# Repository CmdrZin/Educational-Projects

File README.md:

# Educational-Projects
A group of educational projects to promote hardware and software development.
Zip files of projects can be found at [https://www.gameactive.org/dist/](https://www.gameactive.org/dist/)

==================

Educational projects

|        Name          | Description                                                |
|----------------------|------------------------------------------------------------|
| IntroToArduino  | An Educational package on how to program using the Arduino IDE.|
| Beyond Arduino | A guide to learning the AVR series of microcontrollers.|

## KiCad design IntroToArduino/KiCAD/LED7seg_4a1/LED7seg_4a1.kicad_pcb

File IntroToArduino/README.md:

# Introduction to Arduino Project

An educational project with Syllabus, Instructor's guide, and Student Handout for learning coding using the Arduino IDE.

==================

|        Name         | Description                                                |
|---------------------|------------------------------------------------------------|
|DataSheets | Data sheets for devices used in the examples.|  
|ITA\_Examples | Source code for coding projects used in the sections.|   
|KiCAD | KiCAD project source for the helper boards used in the sections.|  
|A000066-full-pinout.pdf | Arduino UNO 3 pin outs.|  
|IntroToArduino.pdf | Syllabus for the course.|  
|IntoToArduino\_Instructor.pdf | Instructor's guide for the course.|  
|IntoToArduino\_Student.pdf | Student handout for the course.|

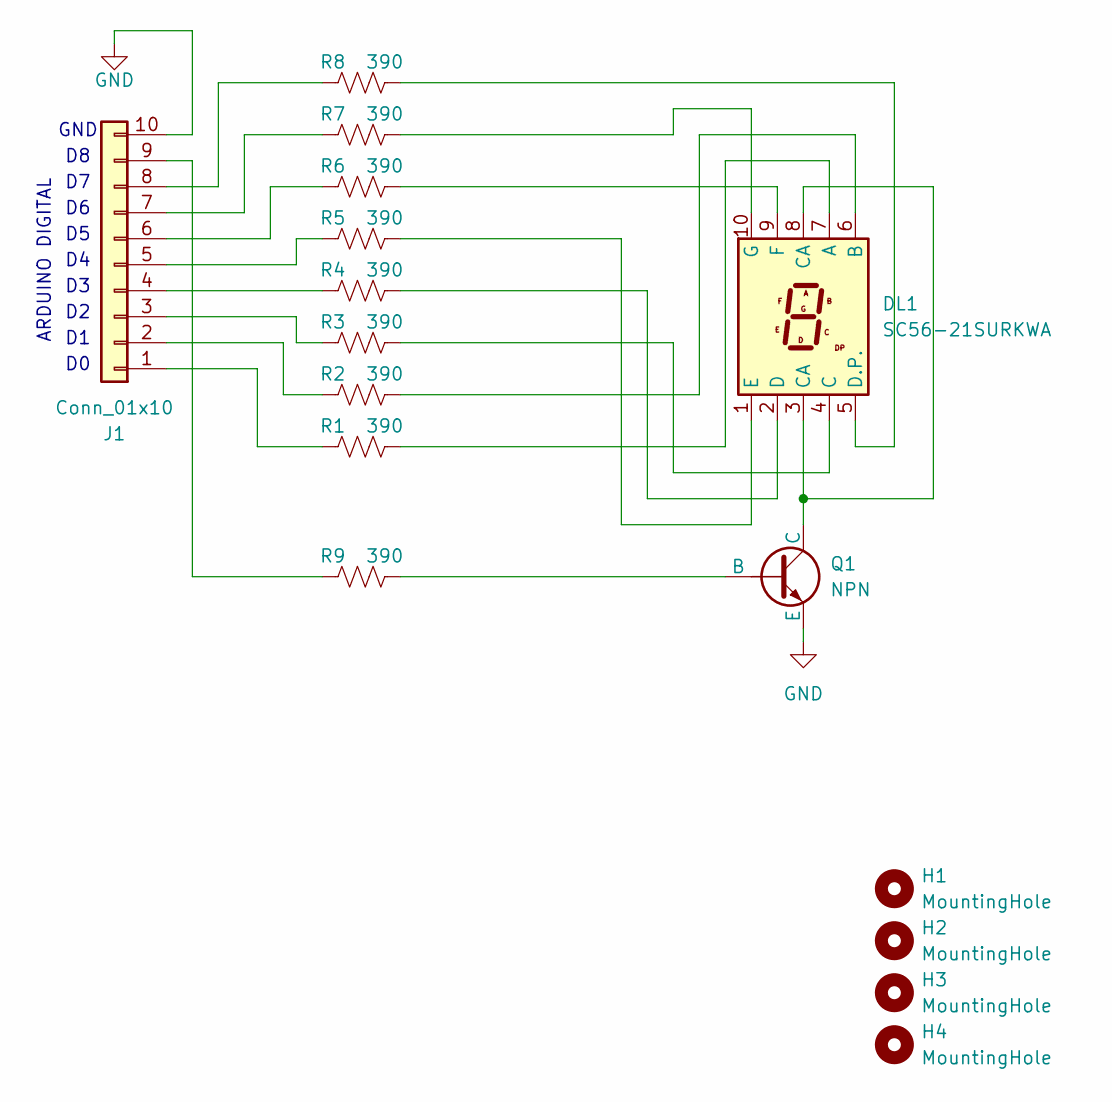
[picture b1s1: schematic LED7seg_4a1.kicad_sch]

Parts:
DL1: SC56-21SURKWA
H1, H2, H3, H4: MountingHole; MountingHole_3.2mm_M3
J1: Conn_01x10; PinSocket_1x10_P2.54mm_Vertical
Q1: NPN; TO-92
R1, R2, R3, R4, R5, R6, R7, R8, R9: 390; R_Axial_DIN0207_L6.3mm_D2.5mm_P10.16mm_Horizontal

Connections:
GND: J1.10, Q1.3 (E)
unnamed: DL1.7 (A), R1.2
unnamed: DL1.6 (B), R2.2
unnamed: DL1.4 (C), R3.2
unnamed: DL1.2 (D), R4.2
unnamed: DL1.5 (D.P.), R8.2
unnamed: DL1.1 (E), R5.2
unnamed: DL1.9 (F), R6.2
unnamed: DL1.10 (G), R7.2
unnamed: J1.1, R1.1
unnamed: J1.2, R2.1
unnamed: J1.3, R3.1
unnamed: J1.4, R4.1
unnamed: J1.5, R5.1
unnamed: J1.6, R6.1
unnamed: J1.7, R7.1
unnamed: J1.8, R8.1
unnamed: J1.9, R9.1
unnamed: Q1.2 (B), R9.2
unnamed: DL1.3 (CA), DL1.8 (CA), Q1.1 (C)

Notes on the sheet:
GND
ARDUINO DIGITAL

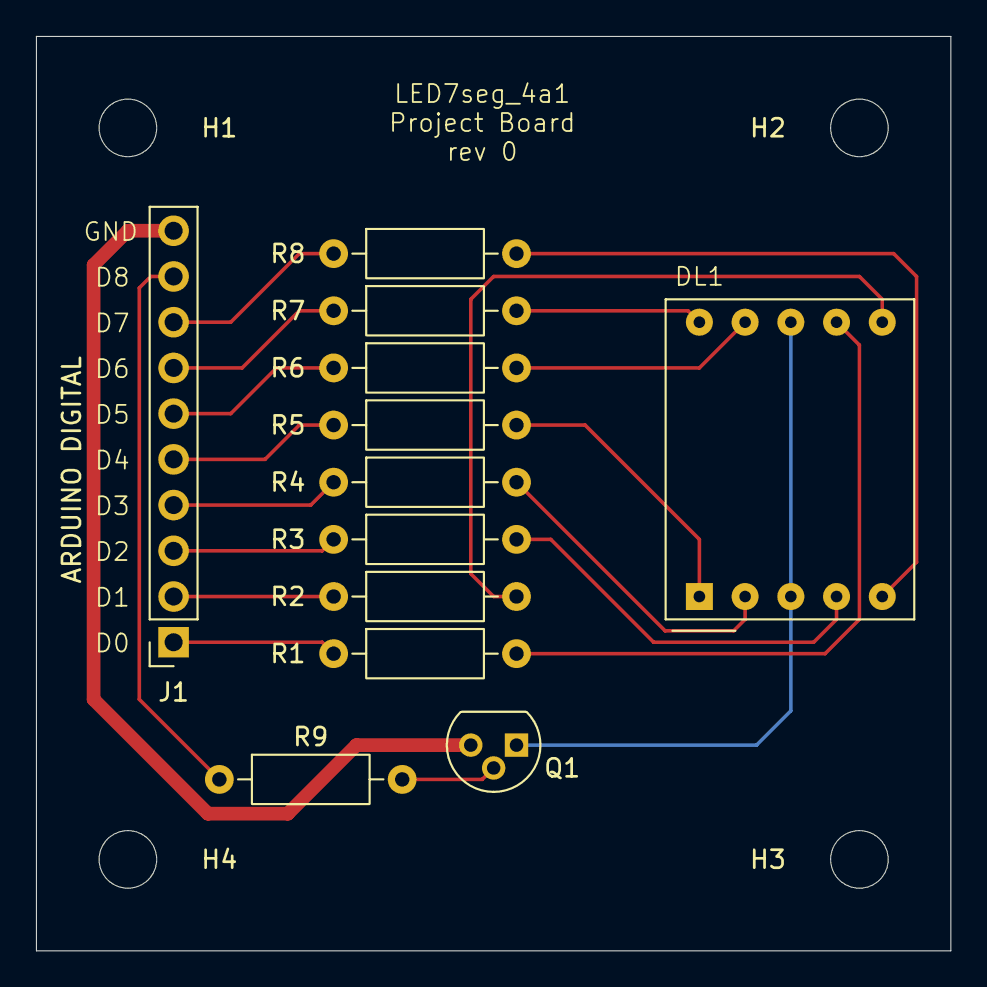
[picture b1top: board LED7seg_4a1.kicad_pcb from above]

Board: 2 copper layers, 50.8 x 50.8 mm, 16 parts (0 on the bottom side), 20 nets.

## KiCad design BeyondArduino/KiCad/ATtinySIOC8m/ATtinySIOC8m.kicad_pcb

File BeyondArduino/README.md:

# Beyond Arduino Project

A guide for learning how to use the Microchip AVR series of microcontrollers.

==================

|        Name         | Description                                                |
|---------------------|------------------------------------------------------------|
|DataSheets | Data sheets for devices used in the examples.|  
|KiCAD | KiCAD project source for the helper boards used in the sections.|  
|Projects | Source code for coding projects used in the sections.|  
|IntroToMC.pdf | Handbook guide.|  
|DDS\_Notes.pdf | Notes for developing DDS for audio generation.|

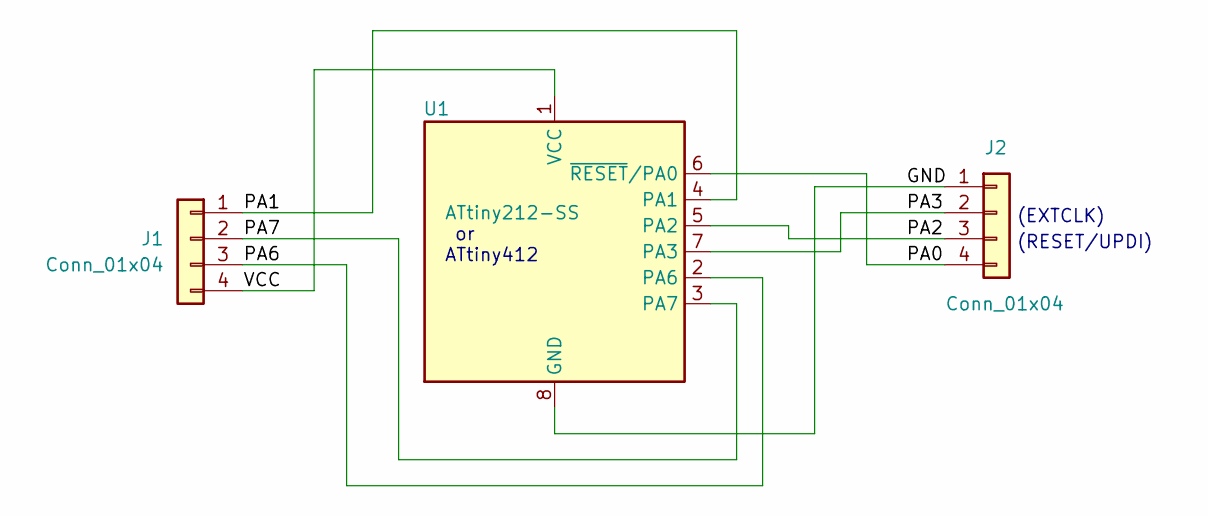
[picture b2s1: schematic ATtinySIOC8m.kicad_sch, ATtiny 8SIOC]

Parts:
J1, J2: Conn_01x04; PinHeader_1x04_P2.54mm_Vertical
U1: ATtiny212-SS; SOIC-8_3.9x4.9mm_P1.27mm

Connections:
/GND: J2.1, U1.8 (GND)
/PA0: J2.4, U1.6 (~RESET/PA0)
/PA1: J1.1, U1.4 (PA1)
/PA2: J2.3, U1.5 (PA2)
/PA3: J2.2, U1.7 (PA3)
/PA6: J1.3, U1.2 (PA6)
/PA7: J1.2, U1.3 (PA7)
/VCC: J1.4, U1.1 (VCC)

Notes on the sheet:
(RESET/UPDI)
(EXTCLK)
or ATtiny412

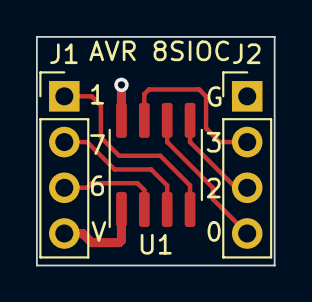
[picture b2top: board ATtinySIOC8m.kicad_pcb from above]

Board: 2 copper layers, 13.2 x 12.7 mm, 3 parts (0 on the bottom side), 8 nets.

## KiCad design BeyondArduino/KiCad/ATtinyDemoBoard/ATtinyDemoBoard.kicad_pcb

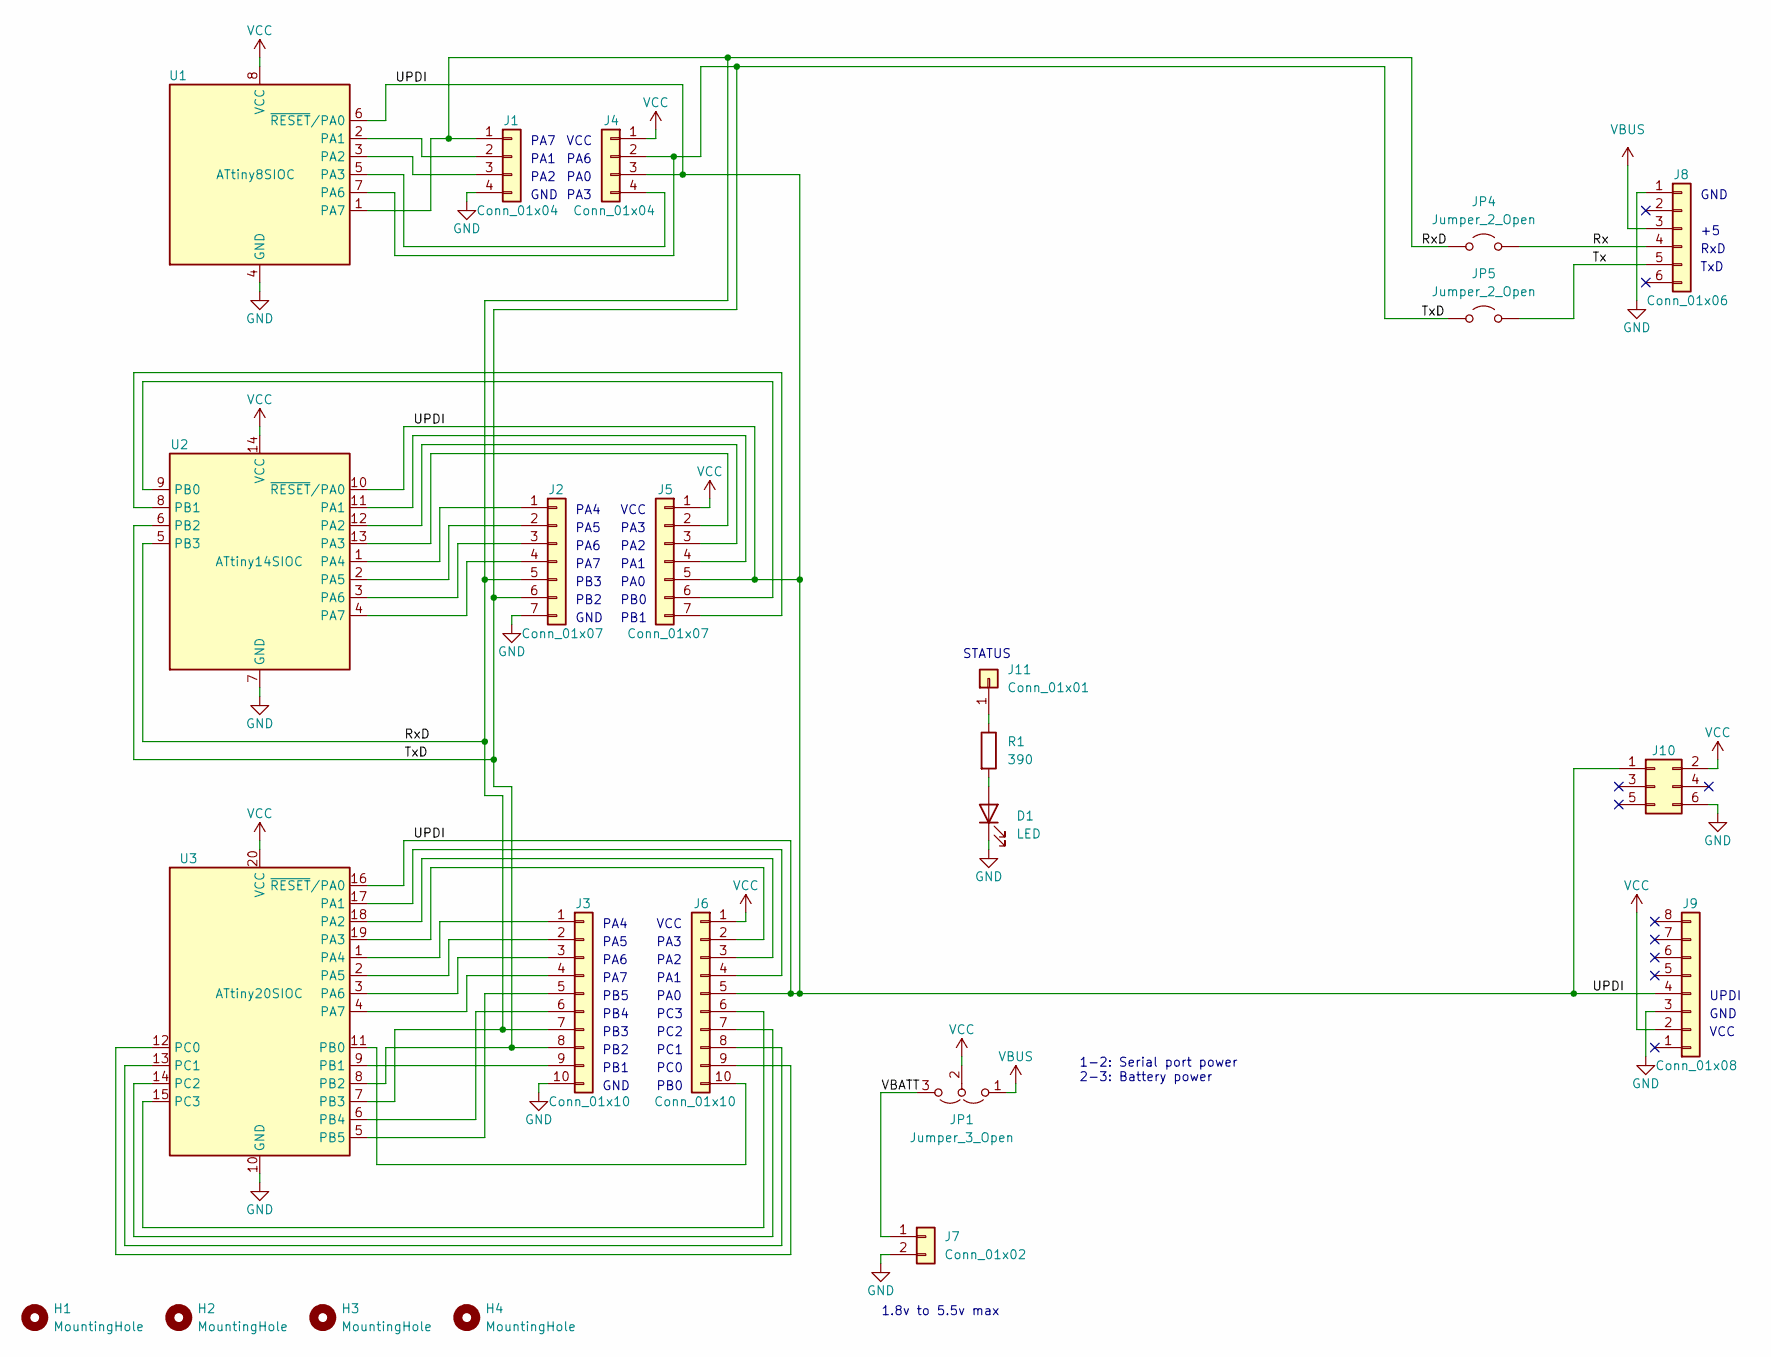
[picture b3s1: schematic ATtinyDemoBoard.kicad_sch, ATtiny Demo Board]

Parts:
D1: LED; D_0805_2012Metric_Pad1.15x1.40mm_HandSolder
H1, H2, H3, H4: MountingHole; MountingHole_3.2mm_M3
J1, J4: Conn_01x04; PinHeader_1x04_P2.54mm_Vertical
J2, J5: Conn_01x07; PinHeader_1x07_P2.54mm_Vertical
J3, J6: Conn_01x10; PinHeader_1x10_P2.54mm_Vertical
J7: Conn_01x02; PinSocket_1x02_P2.54mm_Vertical
J8: Conn_01x06; PinSocket_1x06_P2.54mm_Horizontal__FTDI
J9: Conn_01x08; PinSocket_1x08_P2.54mm_Horizontal
J10: Conn_02x03_Odd_Even; PinHeader_2x03_P2.54mm_Vertical
J11: Conn_01x01; PinSocket_1x01_P2.54mm_Vertical
JP1: Jumper_3_Open; PinSocket_1x03_P2.54mm_Vertical
JP4, JP5: Jumper_2_Open; PinSocket_1x02_P2.54mm_Vertical
R1: 390; R_0805_2012Metric_Pad1.20x1.40mm_HandSolder
U1: ATtiny8SIOC; ATtiny8SIOC-BB
U2: ATtiny14SIOC; ATtiny14SIOC-BB
U3: ATtiny20SIOC; ATtiny20SIOC-BB

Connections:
/Rx: J8.4, JP4.2 (B)
/RxD: J1.1, J2.5, J3.7, JP4.1 (A), U1.1 (PA7), U2.5 (PB3), U3.7 (PB3)
/Tx: J8.5, JP5.2 (B)
/TxD: J2.6, J3.8, J4.2, JP5.1 (A), U1.7 (PA6), U2.6 (PB2), U3.8 (PB2)
/UPDI: J4.3, J5.5, J6.5, J9.4, J10.1, U1.6 (~RESET/PA0), U2.10 (~RESET/PA0), U3.16 (~RESET/PA0)
/VBATT: J7.1, JP1.3 (B)
GND: D1.1 (K), J1.4, J2.7, J3.10, J7.2, J8.1, J9.3, J10.6, U1.4 (GND), U2.7 (GND), U3.10 (GND)
unnamed: D1.2 (A), R1.2
unnamed: J1.2, U1.2 (PA1)
unnamed: J1.3, U1.3 (PA2)
unnamed: J2.1, U2.1 (PA4)
unnamed: J2.2, U2.2 (PA5)
unnamed: J2.3, U2.3 (PA6)
unnamed: J2.4, U2.4 (PA7)
unnamed: J3.1, U3.1 (PA4)
unnamed: J3.2, U3.2 (PA5)
unnamed: J3.3, U3.3 (PA6)
unnamed: J3.4, U3.4 (PA7)
unnamed: J3.5, U3.5 (PB5)
unnamed: J3.6, U3.6 (PB4)
unnamed: J3.9, U3.9 (PB1)
unnamed: J4.4, U1.5 (PA3)
unnamed: J5.2, U2.13 (PA3)
unnamed: J5.3, U2.12 (PA2)
unnamed: J5.4, U2.11 (PA1)
unnamed: J5.6, U2.9 (PB0)
unnamed: J5.7, U2.8 (PB1)
unnamed: J6.2, U3.19 (PA3)
unnamed: J6.3, U3.18 (PA2)
unnamed: J6.4, U3.17 (PA1)
unnamed: J6.6, U3.15 (PC3)
unnamed: J6.7, U3.14 (PC2)
unnamed: J6.8, U3.13 (PC1)
unnamed: J6.9, U3.12 (PC0)
unnamed: J6.10, U3.11 (PB0)
unnamed: J11.1, R1.1
VBUS: J8.3, JP1.1 (A)
VCC: J4.1, J5.1, J6.1, J9.2, J10.2, JP1.2 (C), U1.8 (VCC), U2.14 (VCC), U3.20 (VCC)

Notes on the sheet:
1-2: Serial port power 2-3: Battery power
PC0
PA4
PB0
GND
1.8v to 5.5v max
PA3
VCC
PC3
PA0
PB2
PA7
PB3
PA5
PA2
PB1
UPDI
PA1
PB4
TxD
PA6
PC2
RxD
STATUS
PB5
PC1

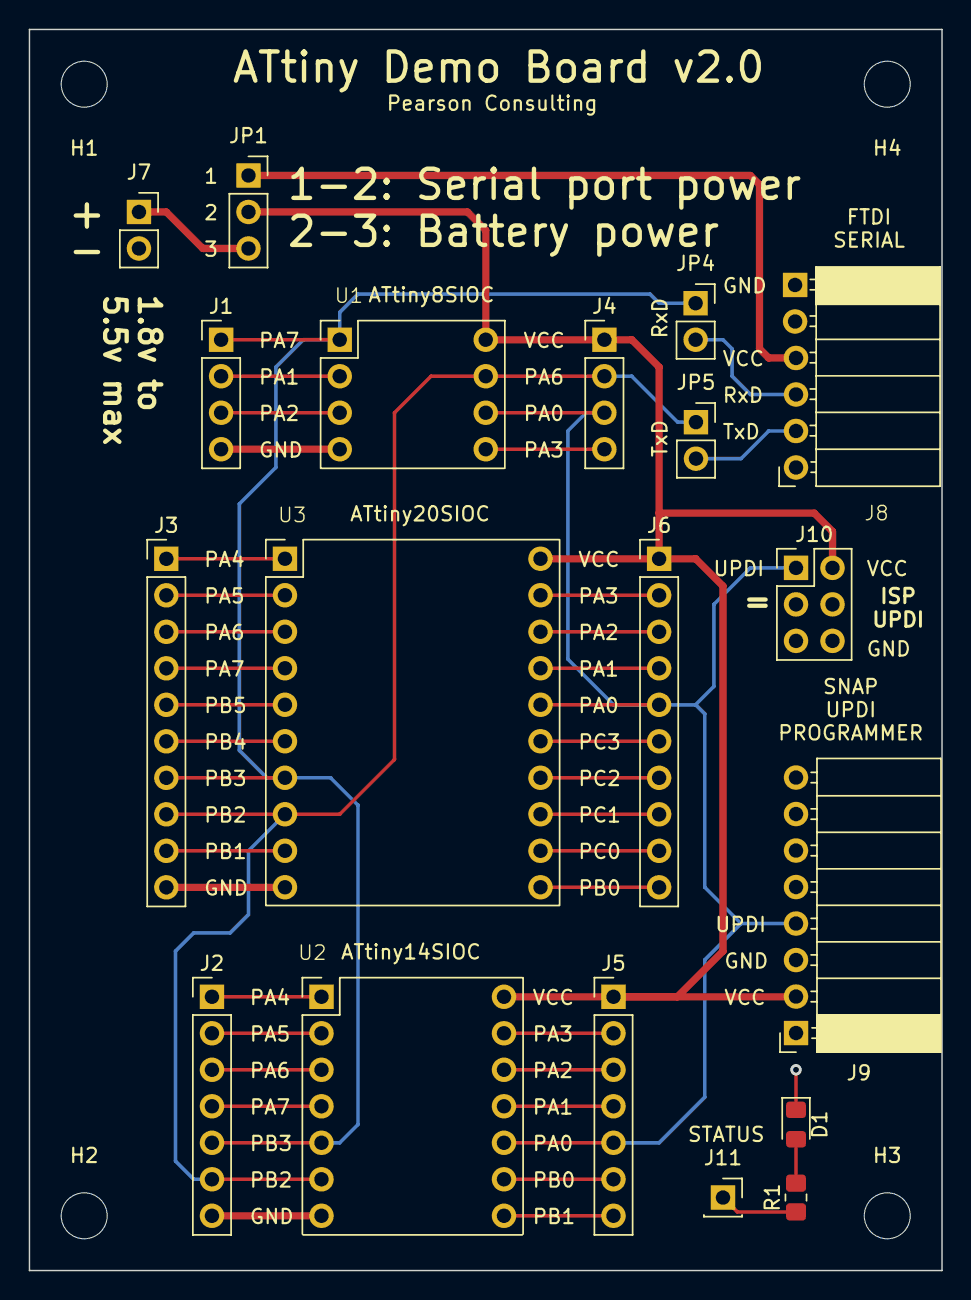
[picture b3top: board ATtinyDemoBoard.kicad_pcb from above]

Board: 2 copper layers, 63.5 x 86.4 mm, 23 parts (0 on the bottom side), 38 nets.

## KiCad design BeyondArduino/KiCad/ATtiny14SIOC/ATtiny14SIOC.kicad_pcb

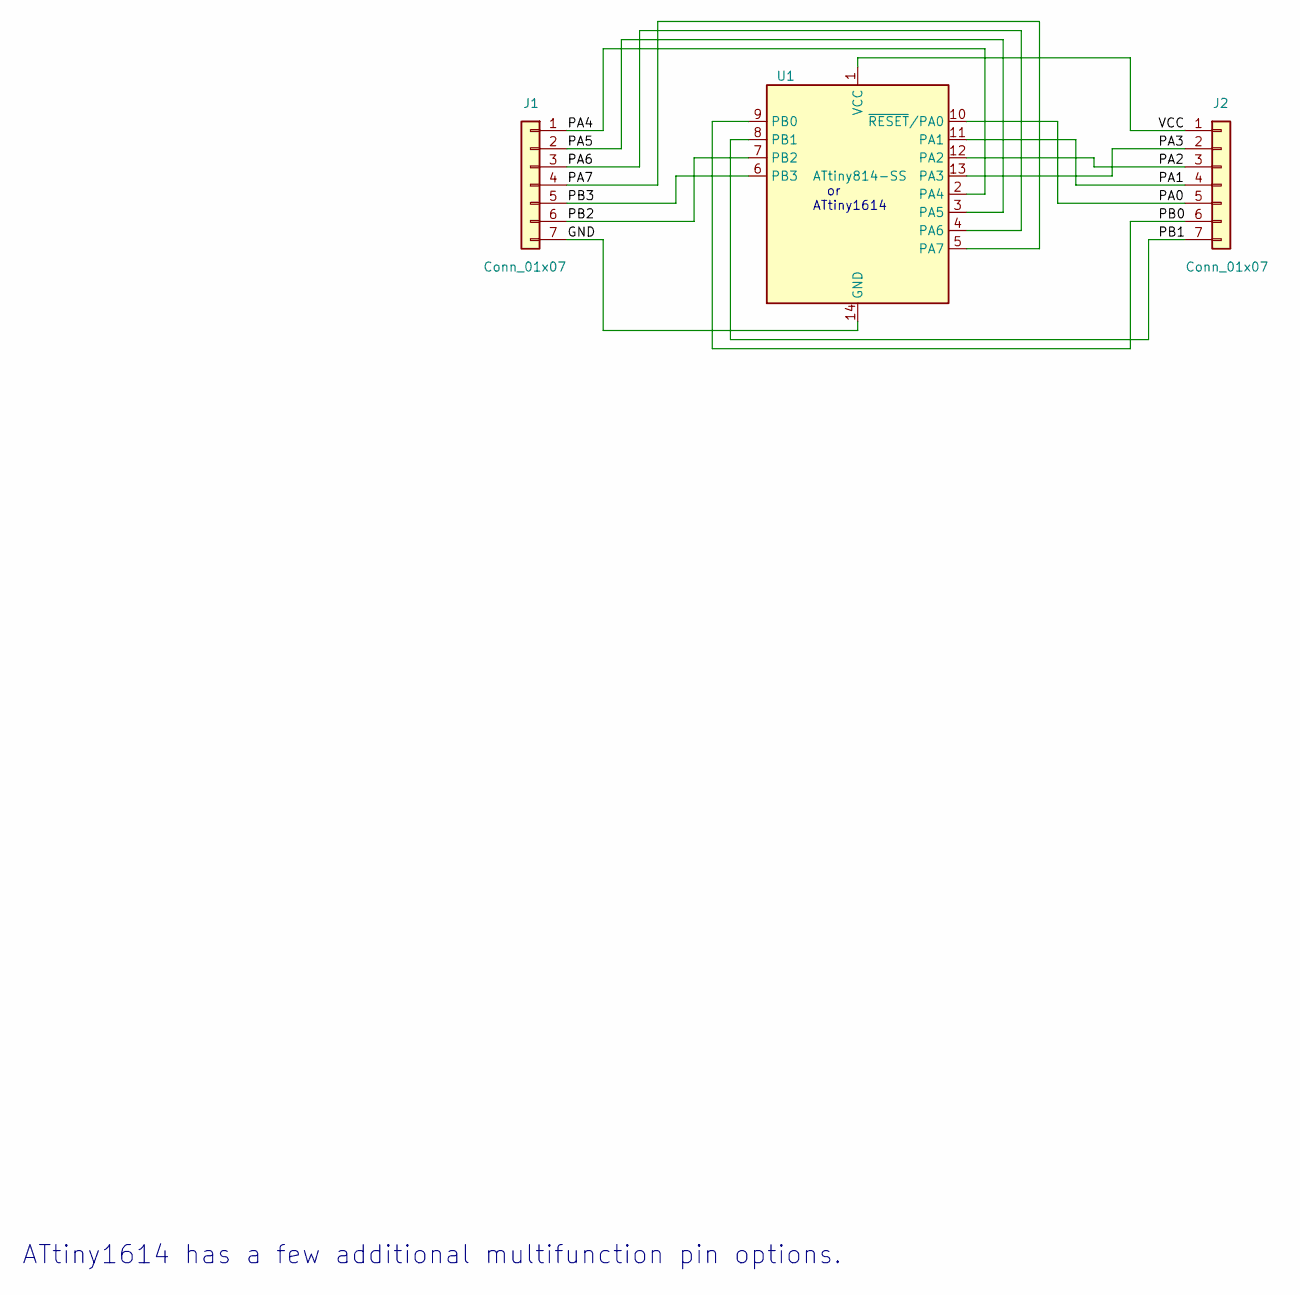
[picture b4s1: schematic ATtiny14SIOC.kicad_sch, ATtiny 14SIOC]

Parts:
J1, J2: Conn_01x07; PinSocket_1x07_P2.54mm_Vertical
U1: ATtiny814-SS; SOIC-14_3.9x8.7mm_P1.27mm

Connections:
/GND: J1.7, U1.14 (GND)
/PA0: J2.5, U1.10 (~RESET/PA0)
/PA1: J2.4, U1.11 (PA1)
/PA2: J2.3, U1.12 (PA2)
/PA3: J2.2, U1.13 (PA3)
/PA4: J1.1, U1.2 (PA4)
/PA5: J1.2, U1.3 (PA5)
/PA6: J1.3, U1.4 (PA6)
/PA7: J1.4, U1.5 (PA7)
/PB0: J2.6, U1.9 (PB0)
/PB1: J2.7, U1.8 (PB1)
/PB2: J1.6, U1.7 (PB2)
/PB3: J1.5, U1.6 (PB3)
/VCC: J2.1, U1.1 (VCC)

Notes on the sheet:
or ATtiny1614
ATtiny1614 has a few additional multifunction pin options.

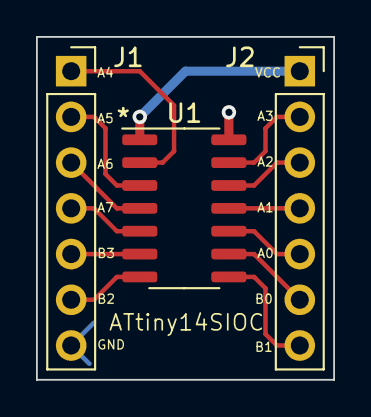
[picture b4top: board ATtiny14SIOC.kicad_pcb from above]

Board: 2 copper layers, 16.5 x 19.0 mm, 3 parts (0 on the bottom side), 14 nets.

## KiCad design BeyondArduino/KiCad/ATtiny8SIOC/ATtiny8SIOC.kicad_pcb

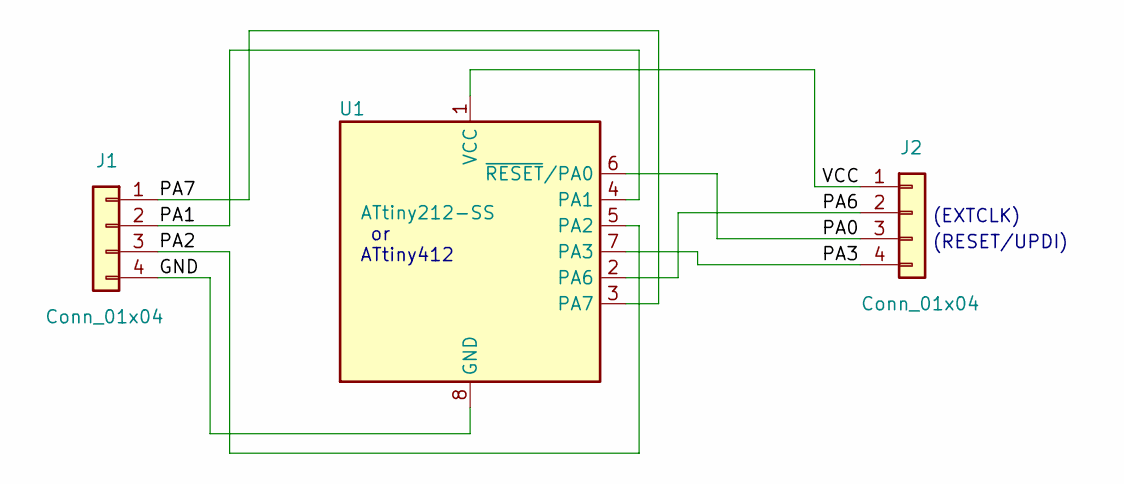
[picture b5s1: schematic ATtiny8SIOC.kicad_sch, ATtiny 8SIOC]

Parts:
J1, J2: Conn_01x04; PinHeader_1x04_P2.54mm_Vertical
U1: ATtiny212-SS; SOIC-8_3.9x4.9mm_P1.27mm

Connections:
/GND: J1.4, U1.8 (GND)
/PA0: J2.3, U1.6 (~RESET/PA0)
/PA1: J1.2, U1.4 (PA1)
/PA2: J1.3, U1.5 (PA2)
/PA3: J2.4, U1.7 (PA3)
/PA6: J2.2, U1.2 (PA6)
/PA7: J1.1, U1.3 (PA7)
/VCC: J2.1, U1.1 (VCC)

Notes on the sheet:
(RESET/UPDI)
(EXTCLK)
or ATtiny412

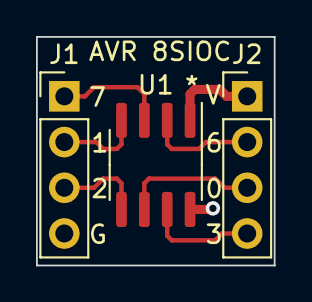
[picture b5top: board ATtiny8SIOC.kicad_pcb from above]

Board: 2 copper layers, 13.2 x 12.7 mm, 3 parts (0 on the bottom side), 8 nets.

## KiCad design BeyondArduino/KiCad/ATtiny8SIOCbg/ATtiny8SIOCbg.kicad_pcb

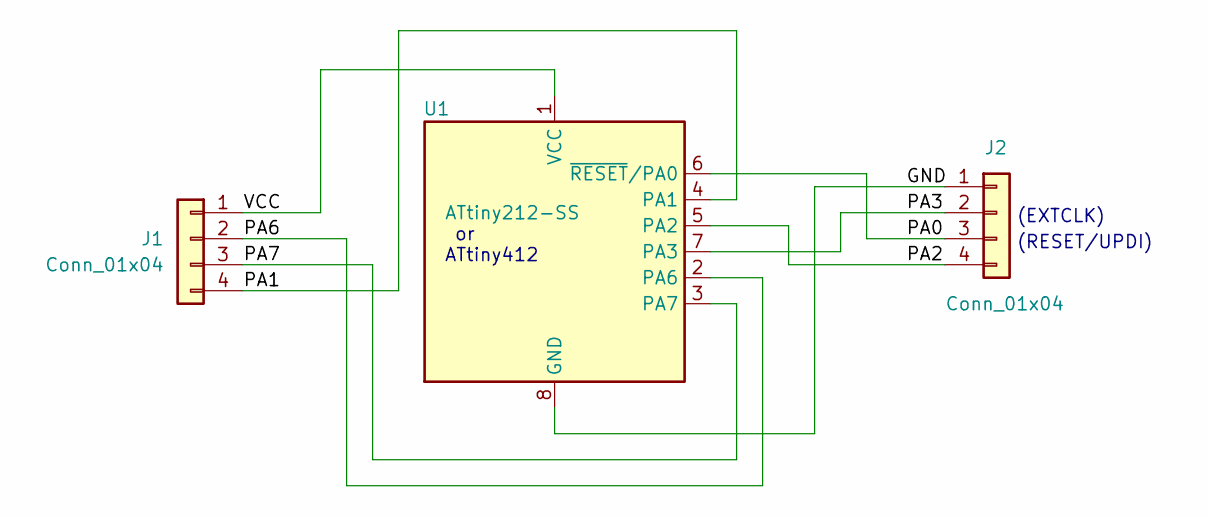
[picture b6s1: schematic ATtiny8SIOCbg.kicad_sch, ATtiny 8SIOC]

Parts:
J1, J2: Conn_01x04; PinHeader_1x04_P2.54mm_Vertical
U1: ATtiny212-SS; SOIC-8_3.9x4.9mm_P1.27mm

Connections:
/GND: J2.1, U1.8 (GND)
/PA0: J2.3, U1.6 (~RESET/PA0)
/PA1: J1.4, U1.4 (PA1)
/PA2: J2.4, U1.5 (PA2)
/PA3: J2.2, U1.7 (PA3)
/PA6: J1.2, U1.2 (PA6)
/PA7: J1.3, U1.3 (PA7)
/VCC: J1.1, U1.1 (VCC)

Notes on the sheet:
(RESET/UPDI)
(EXTCLK)
or ATtiny412

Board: 2 copper layers, 3 parts (0 on the bottom side), 8 nets, no tracks yet.

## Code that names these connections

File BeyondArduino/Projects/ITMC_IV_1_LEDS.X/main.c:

/*
 * File:   main04.c
 * Author: Cmdrzin
 *
 * Created on August 6, 2024
 */


#include <avr/io.h>
#include <avr/interrupt.h>          // to support the use of interrupts
#include <avr/pgmspace.h>

#include "systime.h"                // access systime functions.

#define LED_DELAY		1UL		// N * 1ms
#define LED_ROTATE      200UL

typedef struct LEDconfig {
    uint8_t dir;
    uint8_t lines;
} LED_CONFIG;

//  dir, lines PA:76543210
const LED_CONFIG select[] PROGMEM = {
    { 0b00000110, 0b00000100 },     // D1   PA2->PA1
    { 0b00000110, 0b00000010 },     // D2   PA1->PA2
    { 0b00001100, 0b00000100 },     // D3   PA2->PA3
    { 0b01001000, 0b00001000 },     // D4   PA3->PA6
    { 0b11000000, 0b01000000 },     // D5   PA6->PA7
    { 0b00001010, 0b00001000 },     // D6   PA3->PA1
    { 0b00001100, 0b00001000 },     // D7   PA3->PA2
    { 0b01001000, 0b01000000 },     // D8   PA6->PA3
    { 0b11000000, 0b10000000 },     // D9   PA7->PA6
    { 0b10001000, 0b00001000 },     // D10  PA3->PA7
    { 0b01000010, 0b01000000 },     // D11  PA6->PA1
    { 0b01000100, 0b01000000 },     // D12  PA6->PA2
    { 0b10001000, 0b10000000 },     // D13  PA7->PA3
    { 0b01000100, 0b00000100 },     // D14  PA2->PA6
    { 0b10000100, 0b00000100 },     // D15  PA2->PA7
    { 0b10000010, 0b10000000 },     // D16  PA7->PA1
    { 0b10000100, 0b10000000 },     // D17  PA7->PA2
    { 0b00001010, 0b00000010 },     // D18  PA1->PA3
    { 0b01000010, 0b00000010 },     // D19  PA1->PA6
    { 0b10000010, 0b00000010 }      // D20  PA1->PA7
};
//                               LED   09876543210987654321         
const uint32_t pattern = 0b00000000000010000000000000000000;
uint32_t display;

void nextLED();

int main(void) {
   	uint32_t ledTime = 0UL;
    uint32_t rotateTime = 0UL;
    uint32_t live = pattern;    // copy of starting pattern
    display = live;

    init_systime();             // set up TCA0 timer.
    
    /* enable Global interrupts */
    sei();
   
    // Send out voltage, in HEX, each second.
    while (1) {
		if( millis() > ledTime ) {
			ledTime = millis() + LED_DELAY;
            nextLED();
		}
		if( millis() > rotateTime ) {
			rotateTime = millis() + LED_ROTATE;
            live = live << 1;
            if( (live & 0x00100000) != 0 ) {
                live |= 0x01;
            }
            display = live;
		}
    }
}

// Display the pattern in display.
void nextLED()
{
    uint32_t temp;
    static uint8_t led = 0;
    static LED_CONFIG nextConfig = {0,0};
    uint16_t  adrs;
    uint16_t config;
    
    // First, update display.
    PORTA.DIR = 0;              // turn OFF all lines.
    PORTA.OUT = nextConfig.lines;
    PORTA.DIR = nextConfig.dir;

    // Then calculate next display.
//    adrs = (uint16_t)&select[0];      // this is equivalent to the next line of code.
    adrs = (uint16_t)select;            // get the address of the top of the table.
    adrs = adrs + (led<<1);     // double to skip 2 bytes per index.
    
    temp = display >> led;      // shift display bit to LSB.
    if( temp & 0x0001UL ) {
        config = pgm_read_word_near( adrs );
        nextConfig.dir = (uint8_t)(config & 0x00FF);
        nextConfig.lines = (uint8_t)(config>>8);
    } else {
        nextConfig.dir = 0;
        nextConfig.lines = 0;
    }

    if (++led > 19) {
        led = 0;
    }
}

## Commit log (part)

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2026-01-04 Initial Repository setup
    This repository is for educational projects in development to learn how to use microcontroller hardware and software.
2026-01-04 Update README.md
    Format update
2026-01-06 Added 4b1
    New example file.
2026-01-06 Added 4a2
    Added example of direct hardware control.
2026-02-17 Updated DAC project
    Minor corrections. Completed DAC section and code.
2026-02-17 Updated README.md
    Added link to zip files for projects.
2026-02-18 Updated SPI Client
    Updated SPI Client and fixed minor edits.
2026-02-19 Fixed TCB code
    Verified Section 6a code for the TCB.
2026-02-20 Completed Section III-7
    Completed the WDT and SLEEP section in III-7.
2026-02-21 Verified RTC section
    Reviewed and verified RTC section III-8.
2026-02-22 Updated Section 10
    Finished and tested Section 10 - Analog Comparator.
2026-02-24 Added Section IV_9
    Added section IV_9 on using the RTC_PIT module to generate the millis() 1ms tic to free up the TCA timer.
2026-03-04 README cleanup
2026-03-04 Fixup
2026-03-04 Fixup again
2026-03-11 Fix minor errors
    Fix error in text in EEPROM section.
2026-04-06 Finish IV_13_Quad encoder
    Finish section IV_13_Quad encoder and added Arduino test project for it.
2026-04-06 Fixup ReadMe
    Fix format of Readme file.
2026-04-07 Update ReadMe
    Fix Format of Readme
2026-04-28 updates to Student doc
    Added more comments.
2026-05-10 Added to ITA_Student
    Added more content to Student doc. Improved 3a2 example code.
2026-06-07 Added Section 6 DC Motor control
    Added Section 6 on DC Motor control using a transistor and using an H-Bridge plus a small section on PWM.
2026-06-26 Added Section 5 - Switches
    Added most of Section 5 on Switches and KeyPads.
